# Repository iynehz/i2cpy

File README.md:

# Python I2C library supporting multiple driver implementations

<div>

</div>

## Introduction

I2C is a two-wire protocol for communicating between devices. At the
physical level it consists of 2 wires: SCL and SDA, the clock and data lines
respectively.

I2C objects are created attached to a specific bus. They can be initialized
when created, or initialized later on.

This library is designed to support different I2C driver implementations.
At present below drivers are supported:

* [CH341](https://www.wch-ic.com/downloads/CH341DS1_PDF.html)
* [CH347](https://www.wch-ic.com/downloads/CH347DS1_PDF.html)

The interface is similar to that of MicroPython’s [machine.I2C](https://docs.micropython.org/en/latest/library/machine.I2C.html)

Example usage:

```python
from i2cpy import I2C

i2c = I2C()                      # create I2C peripheral

i2c.writeto(42, b'123')          # write 3 bytes to peripheral with 7-bit address 42
i2c.readfrom(42, 4)              # read 4 bytes from peripheral with 7-bit address 42

i2c.readfrom_mem(42, 8, 3)       # read 3 bytes from memory of peripheral 42,
                                 #   starting at memory address 8 in the peripheral
i2c.writeto_mem(42, 2, b'\x10')  # write 1 byte to memory of peripheral 42,
                                 #   starting at memory address 2 in the peripheral
```

If you prefer an “int” interface to the “bytes” interface, you can easily write
wrapper functions youself. For example,

```python
# assume you already have a gloal i2c object

def i2c_write(addr: int, memaddr: int, *args):
    i2c.writeto_mem(addr, memaddr, bytes(args))

def i2c_read(addr: int, memaddr: int, nbytes: int) -> list[int]:
    got = i2c.readfrom_mem(addr, memaddr, nbytes)
    return list(got)
```

## Installation

The i2cpy Python module itself can be simply pip installed,

```default
pip intall i2cpy
```

And for the underlying I2C implementations you still need to install their
corresponding drivers.

### ch341

The [CH341](https://www.wch-ic.com/products/CH341.html) series chip (like CH341A)
is USB bus converter which converts USB to UART, parallel
port, and common synchronous serial communication interfaces (I2C, SPI).
The chip is manufactured by the company [Qinheng Microelectronics](https://wch-ic.com/).

The “ch341” driver shipped with this library is a Python interface to CH341’s
official DLLs.

You need the driver DLL files, which are downloadable from Qinheng’s website.

* **Windows**: [https://www.wch-ic.com/downloads/CH341PAR_EXE.html](https://www.wch-ic.com/downloads/CH341PAR_EXE.html)

  They also have a zipball [https://www.wch-ic.com/downloads/CH341PAR_ZIP.html](https://www.wch-ic.com/downloads/CH341PAR_ZIP.html) .
  If you use the zipball on Windows it’s recommended to place the DLL files,
  CH341DLLA64.DLL and/or CH341DLL.DLL depending on the bitness, under Windows
  System32/SysWOW64 folder. Or if you place them under a different directory,
  you can add that directory to PATH environment variable.
* **Linux**: [https://www.wch-ic.com/downloads/CH341PAR_LINUX_ZIP.html](https://www.wch-ic.com/downloads/CH341PAR_LINUX_ZIP.html)

  On Linux you need to build the kernel module from source under the downloaded
  zipball’s driver sub-directory like below.
  ```bash
  $ cd driver
  $ sudo rmmod ch34x_pis
  $ make && sudo make install
  ```

  Also you need to either place the libch347.so file for your platform to system
  supported path like /usr/local/lib, or you make the so file loadable by adding
  its directory to LD_LIBRARY_PATH environment variable.

  And because Qinheng sometimes updates their Linux driver and breaks backward
  compatibility, be careful when you upgrade their Linux CH341PAR driver version,
  and make sure your effective libch347.so file and your compiled kernel module
  come from the same driver version.

  Still on Linux there could be more details like, system package
  linux-headers-$(uname -r) being a prerequisite of making the kernel module,
  and permissioning of /dev/ch34x_pis\*, etc..
  Those are beyond scope of this doc though.
* **macOS** is not supported. See also [this ticket](https://github.com/iynehz/i2cpy/issues/3).

Example usage:

```python
from i2cpy import I2C

i2c = I2C()                                     # ch341 is the default driver
i2c = I2C(driver="ch341")                       # explicitly specify driver

i2c = I2C(0)                                    # override usb id

i2c = I2C("/dev/ch34x_pis0")                    # override device path on Linux
```

### ch347

The CH347 series chip (like CH347T) is USB bus converter manufactured also by
Qinheng Microelectronics.

The “ch347” driver shipped with this library is a Python interface to CH347’s
official DLLs.

You need the driver DLL files, which are downloadable from Qinheng’s website.
As they are actually the same downloadable files as that of CH341, see
[ch341](#id1) section above for how to install.

Example usage:

```python
from i2cpy import I2C

i2c = I2C(driver="ch347")                       # specify ch347 driver

i2c = I2C(0, driver="ch347")                    # override usb id

i2c = I2C("/dev/ch34x_pis0", driver="ch347")    # override device path on Linux
```

## Class I2C

### Constructor

#### I2C.\_\_init_\_(id=None, \*, driver=None, freq=400000, auto_init=True, \*\*kwargs)

Constructor.

* **Parameters:**
  * **id** (`Union`[`str`, `int`, `None`]) – Identifies a particular I2C peripheral. Allowed values depend
    on the particular driver implementation.
  * **freq** (`int`) – I2C bus baudrate, defaults to 400000
  * **driver** (`Optional`[`str`]) – I2C driver name. It corresponds to the I2C driver sub
    module name shipped with this library. For example “foo” means module
    “i2cpy.driver.foo”.
    If not specified, it looks at environment variable “I2CPY_DRIVER”.
    And if that’s not defined or is empty, it finally falls back to “ch341”.
  * **auto_init** (`bool`) – Call init() on object initialization, defaults to True

### General methods

#### I2C.init()

Initialize the I2C bus.

#### I2C.deinit()

Close the I2C bus.

#### I2C.scan(start=8, stop=119)

Scan all I2C addresses between start and stop inclusive
and return a list of those that respond.
A device responds if it pulls the SDA line low after its address
(including a write bit) is sent on the bus.

Depending on the specific driver and OS platform, scan() may or may not
work.

* **Parameters:**
  * **start** (`int`) – start address, defaults to 0x08
  * **stop** (`int`) – stop address, defaults to 0x77
* **Return type:**
  `List`[`int`]
* **Returns:**
  a list of addresses that respond to scan

### Standard bus operations

#### I2C.writeto(addr, buf, /)

Write the bytes from buf to the peripheral specified by addr.

* **Parameters:**
  * **addr** (`int`) – I2C peripheral deivce address
  * **buf** (`Buffer`) – bytes to write

#### I2C.readfrom(addr, nbytes, /)

Read nbytes from the peripheral specified by addr.

* **Parameters:**
  * **addr** (`int`) – I2C peripheral device address
  * **nbytes** (`int`) – number of bytes to read
* **Return type:**
  `bytes`
* **Returns:**
  the bytes read

### Memory operations

#### I2C.writeto_mem(addr, memaddr, buf, \*, addrsize=8)

Write buf to the peripheral specified by addr starting from the
memory address specified by memaddr.

* **Parameters:**
  * **addr** (`int`) – I2C peripheral device address
  * **memaddr** (`int`) – memory address
  * **buf** (`Buffer`) – bytes to write
  * **addrsize** (`int`) – address size in bits, defaults to 8

#### I2C.readfrom_mem(addr, memaddr, nbytes, \*, addrsize=8)

Read *nbytes* from the peripheral specified by *addr* starting from
the memory address specified by *memaddr*.

* **Parameters:**
  * **addr** (`int`) – I2C peripheral device address
  * **memaddr** (`int`) – memory address
  * **nbytes** (`int`) – number of bytes to read
  * **addrsize** (`int`) – address size in bits, defaults to 8
* **Return type:**
  `bytes`
* **Returns:**
  the bytes read

#### I2C.readfrom_mem_into(addr, memaddr, buf, \*, addrsize=8)

Read into buf from the peripheral specified by addr starting from the
memory address specified by memaddr. The number of bytes read is the
length of buf.

* **Parameters:**
  * **addr** (`int`) – I2C peripheral device address
  * **memaddr** (`int`) – memory address
  * **buf** (`bytearray`) – buffer to store the bytes read
  * **addrsize** (`int`) – address size in bits, defaults to 8

## Nuitka

If you use [Nuitka](https://nuitka.net/) to package your Python code that uses
i2cpy, you need to specify the implicit-imported module, as otherwise Nuitka
won’t be able to find by itself. For example you can use a
nuitka-package.config.yml file with below content.

```yaml
- module-name: 'i2cpy'
  implicit-imports:
    - depends:
      - 'i2cpy.driver.ch341'
```

And run the nuitka command like,

```cmd
nuitka --standalone --onefile --user-package-configuration-file=nuitka-package.config.yml your_script.py
```

For other packaging tools like Pyinstaller, etc., the idea is similar.

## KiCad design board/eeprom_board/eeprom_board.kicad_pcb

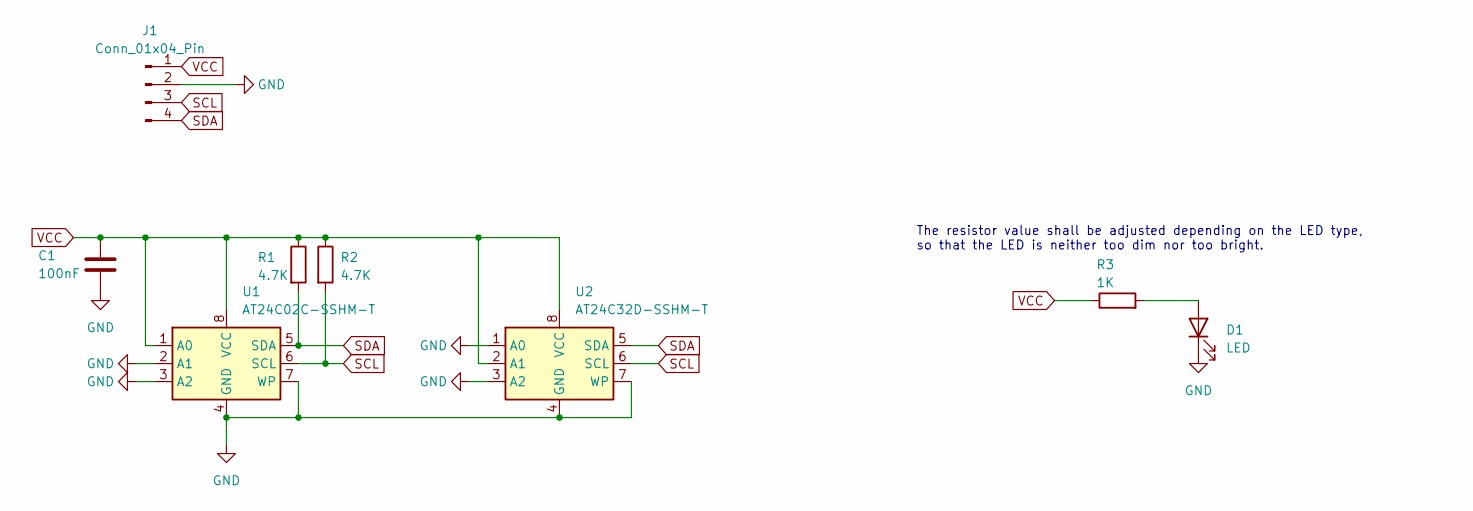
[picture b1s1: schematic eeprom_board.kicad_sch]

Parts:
C1: 100nF; C_0603_1608Metric_Pad1.08x0.95mm_HandSolder
D1: LED; LED_0603_1608Metric_Pad1.05x0.95mm_HandSolder
J1: Conn_01x04_Pin; PinHeader_1x04_P2.54mm_Vertical
R1, R2: 4.7K; R_0603_1608Metric_Pad0.98x0.95mm_HandSolder
R3: 1K; R_0603_1608Metric_Pad0.98x0.95mm_HandSolder
U1: AT24C02C-SSHM-T; SOIC-8_3.9x4.9mm_P1.27mm
U2: AT24C32D-SSHM-T; SOIC-8_3.9x4.9mm_P1.27mm

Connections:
GND: C1.2, D1.1 (K), J1.2, U1.2 (A1), U1.3 (A2), U1.4 (GND), U1.7 (WP), U2.1 (A0), U2.3 (A2), U2.4 (GND), U2.7 (WP)
unnamed: D1.2 (A), R3.2
SCL: J1.3, R2.2, U1.6 (SCL), U2.6 (SCL)
SDA: J1.4, R1.2, U1.5 (SDA), U2.5 (SDA)
VCC: C1.1, J1.1, R1.1, R2.1, R3.1, U1.1 (A0), U1.8 (VCC), U2.2 (A1), U2.8 (VCC)

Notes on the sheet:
The resistor value shall be adjusted depending on the LED type, so that the LED is neither too dim nor too bright.

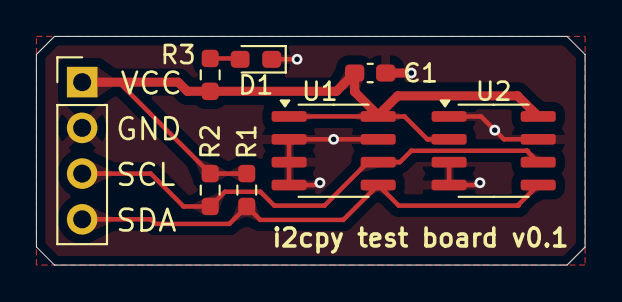
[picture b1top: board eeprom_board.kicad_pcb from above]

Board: 2 copper layers, 30.5 x 12.7 mm, 8 parts (0 on the bottom side), 5 nets.

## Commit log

2024-05-07 ch341 implementation
2024-05-12 wip linux
2024-05-12 fix mypy issues
2024-05-12 linux
2024-05-12 prepare for release
2024-05-13 addr and memaddr type should be int
2024-05-13 github actions
2024-05-13 for mypy change os.name to sys.platform
2024-05-13 update readme badges
2024-05-17 change I2C class constructor signature
2024-05-17 improve I2COperationFailedError
2024-05-17 bump version
2024-05-21 bump version to 0.1.0
2024-06-01 improve package metadata
2024-06-01 bump version to 0.1.1
2024-08-09 restructure doc
2024-08-09 add a changelog
2024-09-30 fix py38 compatibility. and require py>=3.8
2024-09-30 bump version to 0.1.2
2024-09-30 fix python version badge in README
2024-09-30 bump version to 0.1.3
2024-09-30 update changelog
2025-01-28 update README to mention CH341PAR_EXE installer
2025-02-14 fix readfrom_mem() when addrsize is not 8. fixes gh-1
2025-02-14 bump version to 0.1.4
2025-02-24 Update __init__.py
    Adaptation to multiport devices in Linux.
2025-02-24 rework linux device_path thing
2025-02-24 bump version to 0.1.5
2025-04-07 fix py38 compatibility
2025-04-07 add tox setup
2025-04-07 setup tox
2025-04-09 refactor a little bit
2025-04-09 update README to say macOS is not supported
2025-04-09 bump version to 0.1.6
2025-04-09 refresh README
2025-04-09 fix linter issue
2025-04-09 fix tests on windows
2025-04-09 fix a rst link
2025-05-07 fix compatibility with Linux CH341PAR driver version 1.5
2025-05-07 bump version to 0.1.7
2025-07-09 Added ch347 driver
    Tested with 24c64 i2c memory
2025-07-10 Resolved CH347WriteRead issue
    The CH347 dll ha no CH347WriteRead substituted with StreamI2C_RetACK
2025-07-10 ch347: _start() and _stop() are no longer needed as we use CH347StreamI2C_RetACK() for check_device()
2025-07-10 fix ruff check errors, including removing ch347.constants which is not used.
2025-07-11 Restores I2c bus speed setup
2025-07-11 Baudrate error removed
2025-07-13 adopt pyproject.toml's license expression syntax, and bump python min requirement to 3.9, as python 3.8's setuptools does not support it. See also https://github.com/pypa/setuptools/issues/4903
2025-07-13 add to driver supports_scan() method to tell whether the driver can do scan() or not
2025-07-13 fix duplicate 'failed' message on OpenDevice failure
2025-07-13 ch347: align CH347I2CStream_RetACK function name across Windows and Linux
2025-07-13 fix ruff check issues
2025-07-13 ch34x: always check chip type on OpenDevice to make sure it fails with invalid device id or path
2025-07-13 fix mypy error
2025-07-13 update README's python version badge to py39
2025-07-14 Check ACK from device
    Check the acks received from device to test i2c device presence.
    No ack no device present.
2025-07-19 eeprom test board
2025-07-19 fix pyproject.toml
2025-07-19 CHANGELOG: mention v0.2.0's dropping py38
2025-07-20 remove kicad production dir
2025-07-20 ch347: rework ack count check
2025-07-20 bump version to v0.2.1
2025-07-26 fix CH347's datasheet link in README
2025-09-22 update README to mention how to use i2cpy with packaging tools like nuitka or pyinstaller
2025-10-12 trivial doc fix

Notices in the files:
README.md:
License: MIT
